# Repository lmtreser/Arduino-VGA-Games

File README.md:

# Arduino VGA Games

Implementación de videojuegos mediante la biblioteca [VGAX de Sandro Maffiodo](https://github.com/smaffer/vgax), un trabajo de [@Rob+Cai](https://www.instructables.com/member/Rob+Cai/). En el foro de Arduino hay un hilo ["Arduino color game (Bomber) using VGA library"](https://forum.arduino.cc/t/arduino-color-game-bomber-using-vga-library/316899) con más información y distintas versiones de juegos.

Uno de los juegos incluidos es [Pong! de Atari](https://es.wikipedia.org/wiki/Pong), el primer videojuego digital. A diferencia de otros, Pong utilizó un circuito totalmente digital para producir los gráficos, el sonido y el control del juego. No hay software ni CPU, sólo una colección de 66 circuitos integrados discretos que realizan una única función, interconectados para crear el juego que conocemos. En **/docs/PongSchematics.pdf** está el diagrama esquemático de la versión arcade original.

## Algunas fotos del primer prototipo

## Recursos

- Instructable ["VGA Games 4-in-1"](https://www.instructables.com/Arduino-VGA-Games-4-in-1/)
- Instructable ["Pong With Arduino Uno"](https://www.instructables.com/VGA-Pong-with-Arduino-Uno/)
- Biblioteca ["VGAX Library for Arduino UNO and MEGA"](https://github.com/smaffer/vgax)
- Otra biblioteca para explorar: ["APL"](https://github.com/akund/APL)
- Gabinete 3D ["USB paddle game controller"](https://www.thingiverse.com/thing:4223937)
- [The original Pong video game had no code](https://www.reddit.com/r/EngineeringPorn/comments/ul49zt/the_original_pong_video_game_had_no_code_and_was/)
- [Fabricating Hardware From The Original Arcade Pong Schematics](https://hackaday.com/2012/12/22/fabricating-hardware-from-the-original-arcade-pong-schematics/)

## Licencia

Tanto la **biblioteca VGAX** como el **firmware original de Rob+Cai** están protegidas por sus respectivas licencias, por favor consulte los sitios donde se alojan para mayor información. El resto del trabajo está protegido por la **Licencia MIT**. Puedes acceder a la versión original de la licencia (en inglés) a través del archivo [LICENSE](./LICENSE) o en línea en [The MIT License (MIT)](https://mit-license.org/). También proporcionamos una traducción no oficial desde [Wikipedia](https://es.m.wikipedia.org/wiki/Licencia_MIT#La_licencia):

Copyright (c) 2024 Lucas Martín Treser

Por la presente se concede permiso, libre de cargos, a cualquier persona que obtenga una copia de este software y de los archivos de documentación asociados (el "Software"), a utilizar el Software sin restricción, incluyendo sin limitación los derechos a usar, copiar, modificar, fusionar, publicar, distribuir, sublicenciar, y/o vender copias del Software, y a permitir a las personas a las que se les proporcione el Software a hacer lo mismo, sujeto a las siguientes condiciones:

El aviso de copyright anterior y este aviso de permiso se incluirán en todas las copias o partes sustanciales del Software.

EL SOFTWARE SE PROPORCIONA "COMO ESTÁ", SIN GARANTÍA DE NINGÚN TIPO, EXPRESA O IMPLÍCITA, INCLUYENDO PERO NO LIMITADO A GARANTÍAS DE COMERCIALIZACIÓN, IDONEIDAD PARA UN PROPÓSITO PARTICULAR E INCUMPLIMIENTO. EN NINGÚN CASO LOS AUTORES O PROPIETARIOS DE LOS DERECHOS DE AUTOR SERÁN RESPONSABLES DE NINGUNA RECLAMACIÓN, DAÑOS U OTRAS RESPONSABILIDADES, YA SEA EN UNA ACCIÓN DE CONTRATO, AGRAVIO O CUALQUIER OTRO MOTIVO, DERIVADAS DE, FUERA DE O EN CONEXIÓN CON EL SOFTWARE O SU USO U OTRO TIPO DE ACCIONES EN EL SOFTWARE.

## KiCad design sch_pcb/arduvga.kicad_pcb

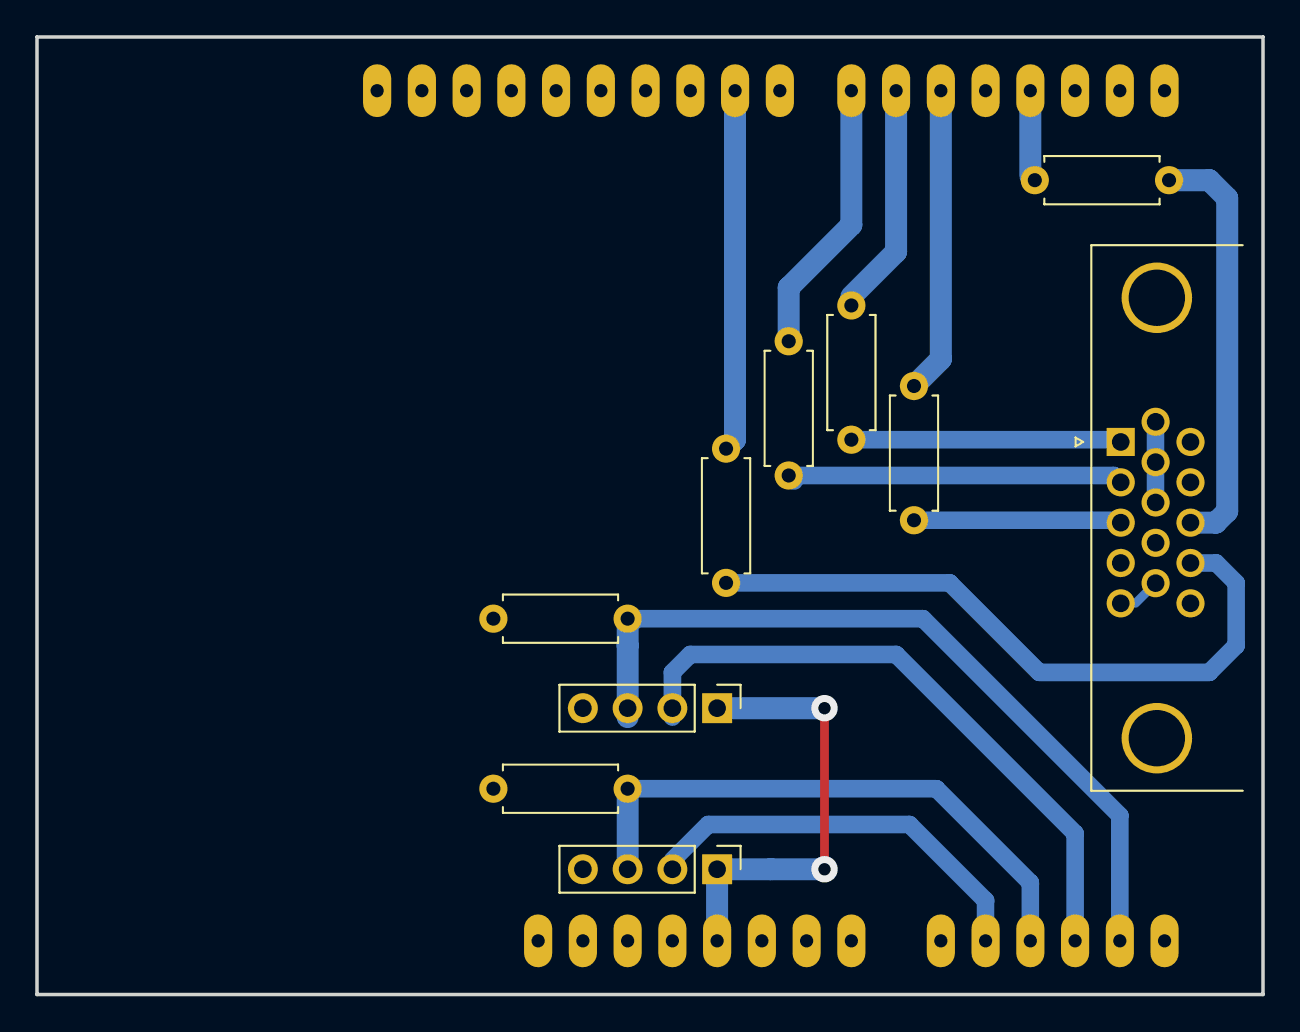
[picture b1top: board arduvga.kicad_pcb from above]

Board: 2 copper layers, 69.6 x 54.4 mm, 11 parts (1 on the bottom side), 16 nets.

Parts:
A1: Arduino UNO R3; Arduino_UNO_R3_OVAL
J1, J3: Conn_01x04_Socket; PinHeader_1x04_P2.54mm_Vertical
J5: DSUB15; DSUB-15-HD_Female_Horizontal_P2.29x1.98mm_EdgePinOffset3.03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
R1, R4: 68; R_Axial_DIN0207_L6.3mm_D2.5mm_P7.62mm_Horizontal
R2, R3, R7: 470; R_Axial_DIN0207_L6.3mm_D2.5mm_P7.62mm_Horizontal
R5, R6: 1k8; R_Axial_DIN0207_L6.3mm_D2.5mm_P7.62mm_Horizontal

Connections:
+5V: A1.5 (+5V), J1.1, J3.1
GND: A1.6 (GND), A1.7 (GND), A1.29 (GND), J1.4, J3.4, J5.0, J5.5, J5.6, J5.7, J5.8, J5.10, R5.2, R6.2
unnamed: A1.10 (A1), J1.2
unnamed: A1.11 (A2), J1.3, R5.1
unnamed: A1.12 (A3), J3.2
unnamed: A1.18 (D3), R1.2
unnamed: A1.20 (D5), R7.2
unnamed: A1.21 (D6), R2.2
unnamed: A1.22 (D7), R3.2
unnamed: A1.24 (D9), R4.2
unnamed: A1.13 (SDA/A4), J3.3, R6.1
unnamed: J5.1, R2.1
unnamed: J5.2, R3.1
unnamed: J5.3, R7.1
unnamed: J5.13, R1.1
unnamed: J5.14, R4.1

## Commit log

2024-01-09 documentación
2024-01-09 Biblioteca VGAx y ejemplos de aplicacion
2024-01-09 KiCad v7 sch brd
2024-01-10 Gabinete Joysticks
2024-01-10 update sch
2024-01-11 Primeras pruebas
2024-01-11 update pcb
2024-01-11 Plantilla para fabricacion
2024-01-13 add arduino uno footprint
2024-01-13 remove images
2024-01-16 update case files
2024-01-16 case gcode
2024-01-16 add photos
2024-01-17 update readme e imagenes
2024-01-17 add pong_VGAx_v1.1
2024-01-17 add pong_VGAx_v1.3
2024-01-18 add schematic diagram for the original arcade version of Pong
2024-02-01 Create LICENSE
2024-05-16 add gbr, step files
2024-05-16 add poster files
2024-05-17 add cam files
2024-05-21 add flatcam screenshot
2024-05-31 add renders
